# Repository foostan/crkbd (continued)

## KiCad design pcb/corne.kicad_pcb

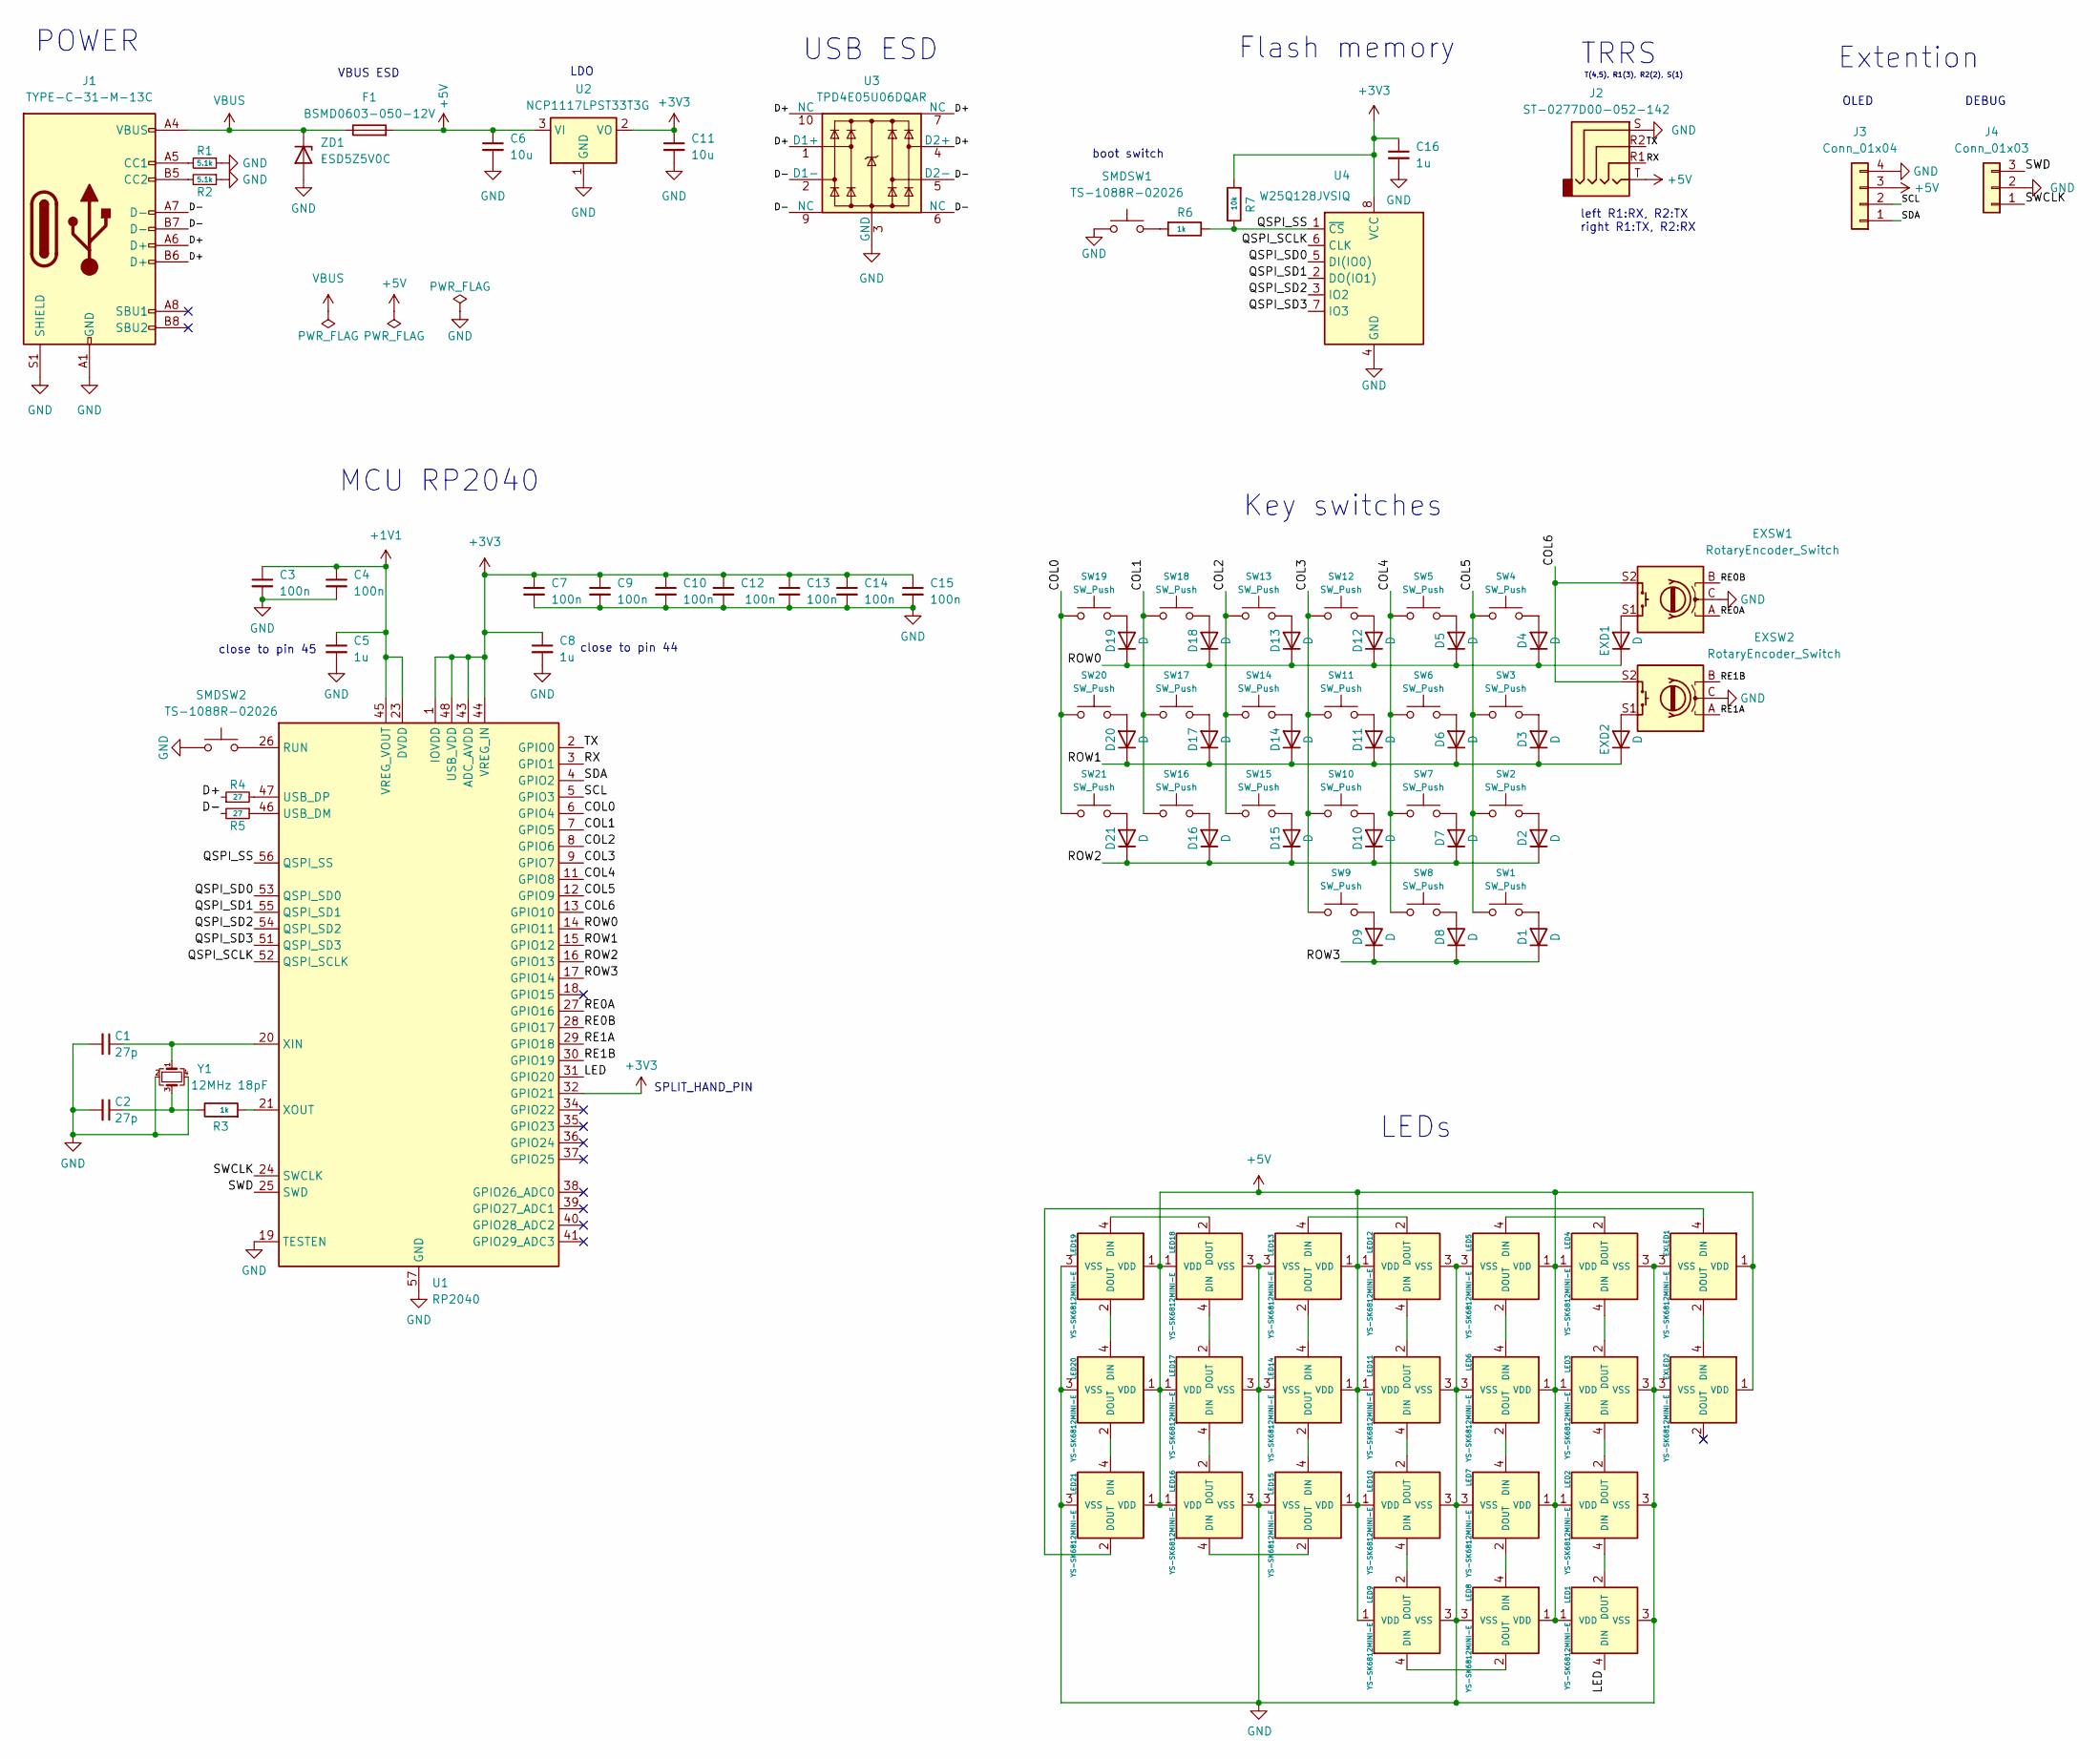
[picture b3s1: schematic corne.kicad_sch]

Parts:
C1, C2: 27p; C_0402_1005Metric
C3, C4, C7, C9, C10, C12, C13, C14, C15: 100n; C_0402_1005Metric
C5, C8, C16: 1u; C_0402_1005Metric
C6, C11: 10u; C_0402_1005Metric
D1, D2, D3, D4, D5, D6, D7, D8, D9, D10, D11, D12, D13, D14, D15, D16, D17, D18, D19, D20, D21: D; D_0603_1608Metric
EXD1, EXD2: D; D_0603_1608Metric
EXLED1, EXLED2: YS-SK6812MINI-E
EXSW1, EXSW2: RotaryEncoder_Switch; keyswitch_cherrymx_hotswap_1u_rotary_encoder_ec12
F1: BSMD0603-050-12V; Fuse_0603_1608Metric; JLCPCB Part # C2844464
J1: TYPE-C-31-M-13C; JLCPCB Part # C2848620
J2: ST-0277D00-052-142; JLCPCB Part # C2837093
J3: Conn_01x04; OLED
J4: Conn_01x03; PinHeader_1x03_P2.54mm_Vertical
LED1, LED2, LED3, LED4, LED5, LED6, LED7, LED8, LED9, LED10, LED11, LED12, LED13, LED14, LED15, LED16, LED17, LED18, LED19, LED20, LED21: YS-SK6812MINI-E
R1, R2: 5.1k; R_0603_1608Metric
R3, R6: 1k; R_0603_1608Metric
R4, R5: 27; R_0603_1608Metric
R7: 10k; R_0603_1608Metric
SMDSW1, SMDSW2: TS-1088R-02026; JLCPCB Part # C455280
SW1: SW_Push; keyswitch_cherrymx_hotswap_1.5u
SW2, SW3, SW4, SW5, SW6, SW7, SW8, SW9, SW10, SW11, SW12, SW13, SW14, SW15, SW16, SW17, SW18, SW19, SW20, SW21: SW_Push; keyswitch_cherrymx_hotswap_1u
U1: RP2040; QFN-56-1EP_7x7mm_P0.4mm_EP3.2x3.2mm; JLCPCB Part # C2040
U2: NCP1117LPST33T3G; SOT-223-3_TabPin2; JLCPCB Part # C146799
U3: TPD4E05U06DQAR; USON-10_2.5x1.0mm_P0.5mm; JLCPCB Part # C138714
U4: W25Q128JVSIQ; SOIC-8_5.23x5.23mm_P1.27mm; JLCPCB Part # C113767
Y1: 12MHz 18pF; Crystal_SMD_3225-4Pin_3.2x2.5mm; MFR.Part # Q22FA23V0041800; JLCPCB Part # C91749
ZD1: ESD5Z5V0C; D_SOD-523; JLCPCB Part # C2901325

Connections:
+1V1: C3.1, C4.1, C5.1, U1.23 (DVDD), U1.45 (VREG_VOUT), U1.50 (DVDD)
+3V3: C7.1, C8.1, C9.1, C10.1, C11.1, C12.1, C13.1, C14.1, C15.1, C16.1, R7.2, U1.1 (IOVDD), U1.10 (IOVDD), U1.22 (IOVDD), U1.32 (GPIO21), U1.33 (IOVDD), U1.42 (IOVDD), U1.43 (ADC_AVDD), U1.44 (VREG_IN), U1.48 (USB_VDD), U1.49 (IOVDD), U2.2 (VO), U4.8 (VCC)
+5V: C6.1, EXLED1.1 (VDD), EXLED2.1 (VDD), F1.2, J2.T, J3.3, LED1.1 (VDD), LED2.1 (VDD), LED3.1 (VDD), LED4.1 (VDD), LED5.1 (VDD), LED6.1 (VDD), LED7.1 (VDD), LED8.1 (VDD), LED9.1 (VDD), LED10.1 (VDD), LED11.1 (VDD), LED12.1 (VDD), LED13.1 (VDD), LED14.1 (VDD), LED15.1 (VDD), LED16.1 (VDD), LED17.1 (VDD), LED18.1 (VDD), LED19.1 (VDD), LED20.1 (VDD), LED21.1 (VDD), U2.3 (VI)
/COL0: SW19.1, SW20.1, SW21.1, U1.6 (GPIO4)
/COL1: SW16.1, SW17.1, SW18.1, U1.7 (GPIO5)
/COL2: SW13.1, SW14.1, SW15.1, U1.8 (GPIO6)
/COL3: SW9.1, SW10.1, SW11.1, SW12.1, U1.9 (GPIO7)
/COL4: SW5.1, SW6.1, SW7.1, SW8.1, U1.11 (GPIO8)
/COL5: SW1.1, SW2.1, SW3.1, SW4.1, U1.12 (GPIO9)
/COL6: EXSW1.S2, EXSW2.S2, U1.13 (GPIO10)
/D+: J1.A6 (D+), J1.B6 (D+), R4.1, U3.1 (D1+), U3.4 (D2+), U3.7 (NC), U3.10 (NC)
/D-: J1.A7 (D-), J1.B7 (D-), R5.2, U3.2 (D1-), U3.5 (D2-), U3.6 (NC), U3.9 (NC)
/LED: LED1.4 (DIN), U1.31 (GPIO20)
/QSPI_SCLK: U1.52 (QSPI_SCLK), U4.6 (CLK)
/QSPI_SD0: U1.53 (QSPI_SD0), U4.5 (DI(IO0))
/QSPI_SD1: U1.55 (QSPI_SD1), U4.2 (DO(IO1))
/QSPI_SD2: U1.54 (QSPI_SD2), U4.3 (IO2)
/QSPI_SD3: U1.51 (QSPI_SD3), U4.7 (IO3)
/QSPI_SS: R6.1, R7.1, U1.56 (QSPI_SS), U4.1 (~CS)
/RE0A: EXSW1.A, U1.27 (GPIO16)
/RE0B: EXSW1.B, U1.28 (GPIO17)
/RE1A: EXSW2.A, U1.29 (GPIO18)
/RE1B: EXSW2.B, U1.30 (GPIO19)
/ROW0: D4.1 (K), D5.1 (K), D12.1 (K), D13.1 (K), D18.1 (K), D19.1 (K), EXD1.1 (K), U1.14 (GPIO11)
/ROW1: D3.1 (K), D6.1 (K), D11.1 (K), D14.1 (K), D17.1 (K), D20.1 (K), EXD2.1 (K), U1.15 (GPIO12)
/ROW2: D2.1 (K), D7.1 (K), D10.1 (K), D15.1 (K), D16.1 (K), D21.1 (K), U1.16 (GPIO13)
/ROW3: D1.1 (K), D8.1 (K), D9.1 (K), U1.17 (GPIO14)
/RX: J2.R1, U1.3 (GPIO1)
/SCL: J3.2, U1.5 (GPIO3)
/SDA: J3.1, U1.4 (GPIO2)
/SWCLK: J4.1, U1.24 (SWCLK)
/SWD: J4.3, U1.25 (SWD)
/TX: J2.R2, U1.2 (GPIO0)
GND: C1.2, C2.2, C3.2, C4.2, C5.2, C6.2, C7.2, C8.2, C9.2, C10.2, C11.2, C12.2, C13.2, C14.2, C15.2, C16.2, EXLED1.3 (VSS), EXLED2.3 (VSS), EXSW1.C, EXSW2.C, J1.A1 (GND), J1.A12 (GND), J1.B1 (GND), J1.B12 (GND), J1.S1 (SHIELD), J2.S, J3.4, J4.2, LED1.3 (VSS), LED2.3 (VSS), LED3.3 (VSS), LED4.3 (VSS), LED5.3 (VSS), LED6.3 (VSS), LED7.3 (VSS), LED8.3 (VSS), LED9.3 (VSS), LED10.3 (VSS), LED11.3 (VSS), LED12.3 (VSS), LED13.3 (VSS), LED14.3 (VSS), LED15.3 (VSS), LED16.3 (VSS), LED17.3 (VSS), LED18.3 (VSS), LED19.3 (VSS), LED20.3 (VSS), LED21.3 (VSS), R1.1, R2.1, SMDSW1.1, SMDSW2.1, U1.19 (TESTEN), U1.57 (GND), U2.1 (GND), U3.3 (GND), U3.8 (GND), U4.4 (GND), Y1.2, Y1.4, ZD1.2 (A)
unnamed: C2.1, R3.1, Y1.3
unnamed: D1.2 (A), SW1.2
unnamed: D2.2 (A), SW2.2
unnamed: D3.2 (A), SW3.2
unnamed: D4.2 (A), SW4.2
unnamed: D5.2 (A), SW5.2
unnamed: D6.2 (A), SW6.2
unnamed: D7.2 (A), SW7.2
unnamed: D8.2 (A), SW8.2
unnamed: D9.2 (A), SW9.2
unnamed: D10.2 (A), SW10.2
unnamed: D11.2 (A), SW11.2
unnamed: D12.2 (A), SW12.2
unnamed: D13.2 (A), SW13.2
unnamed: D14.2 (A), SW14.2
unnamed: D15.2 (A), SW15.2
unnamed: D16.2 (A), SW16.2
unnamed: D17.2 (A), SW17.2
unnamed: D18.2 (A), SW18.2
unnamed: D19.2 (A), SW19.2
unnamed: D20.2 (A), SW20.2
unnamed: D21.2 (A), SW21.2
unnamed: EXD1.2 (A), EXSW1.S1
unnamed: EXD2.2 (A), EXSW2.S1
unnamed: EXLED1.4 (DIN), LED21.2 (DOUT)
unnamed: EXLED1.2 (DOUT), EXLED2.4 (DIN)
unnamed: J1.A5 (CC1), R1.2
unnamed: J1.B5 (CC2), R2.2
unnamed: LED1.2 (DOUT), LED2.4 (DIN)
unnamed: LED2.2 (DOUT), LED3.4 (DIN)
unnamed: LED3.2 (DOUT), LED4.4 (DIN)
unnamed: LED4.2 (DOUT), LED5.4 (DIN)
unnamed: LED5.2 (DOUT), LED6.4 (DIN)
unnamed: LED6.2 (DOUT), LED7.4 (DIN)
unnamed: LED7.2 (DOUT), LED8.4 (DIN)
unnamed: LED8.2 (DOUT), LED9.4 (DIN)
unnamed: LED9.2 (DOUT), LED10.4 (DIN)
unnamed: LED10.2 (DOUT), LED11.4 (DIN)
unnamed: LED11.2 (DOUT), LED12.4 (DIN)
unnamed: LED12.2 (DOUT), LED13.4 (DIN)
unnamed: LED13.2 (DOUT), LED14.4 (DIN)
unnamed: LED14.2 (DOUT), LED15.4 (DIN)
unnamed: LED15.2 (DOUT), LED16.4 (DIN)
unnamed: LED16.2 (DOUT), LED17.4 (DIN)
unnamed: LED17.2 (DOUT), LED18.4 (DIN)
unnamed: LED18.2 (DOUT), LED19.4 (DIN)
unnamed: LED19.2 (DOUT), LED20.4 (DIN)
unnamed: LED20.2 (DOUT), LED21.4 (DIN)
unnamed: R6.2, SMDSW1.2
unnamed: SMDSW2.2, U1.26 (RUN)
unnamed: R5.1, U1.46 (USB_DM)
unnamed: R4.2, U1.47 (USB_DP)
unnamed: C1.1, U1.20 (XIN), Y1.1
unnamed: R3.2, U1.21 (XOUT)
VBUS: F1.1, J1.A4 (VBUS), J1.A9 (VBUS), J1.B4 (VBUS), J1.B9 (VBUS), ZD1.1 (K)

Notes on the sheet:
TRRS
left R1:RX, R2:TX right R1:TX, R2:RX
POWER
close to pin 44
T(4,5), R1(3), R2(2), S(1)
LDO
USB ESD
boot switch
DEBUG
Key switches
SPLIT_HAND_PIN
Flash memory
close to pin 45
Extention
LEDs
MCU RP2040
VBUS ESD
OLED

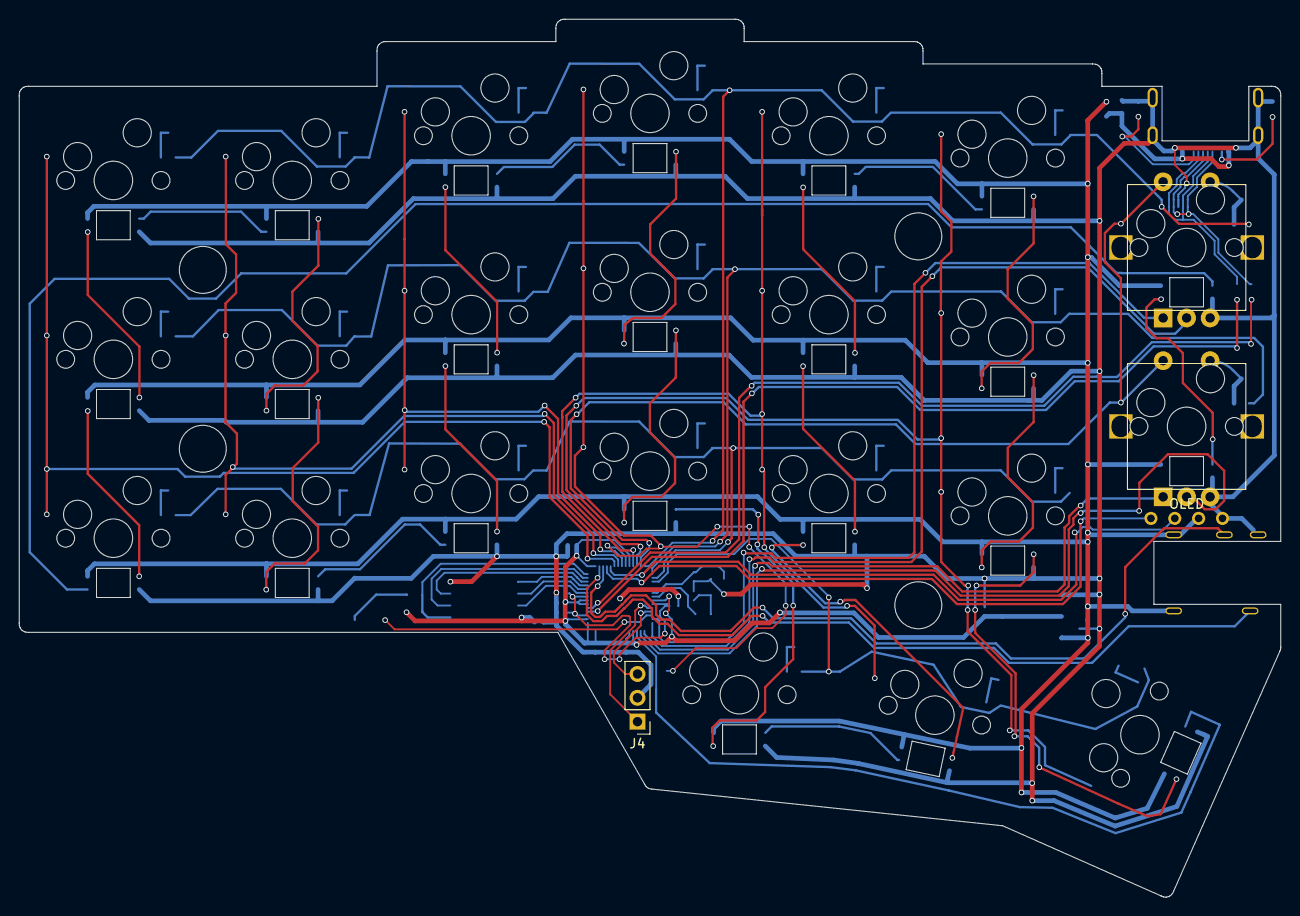
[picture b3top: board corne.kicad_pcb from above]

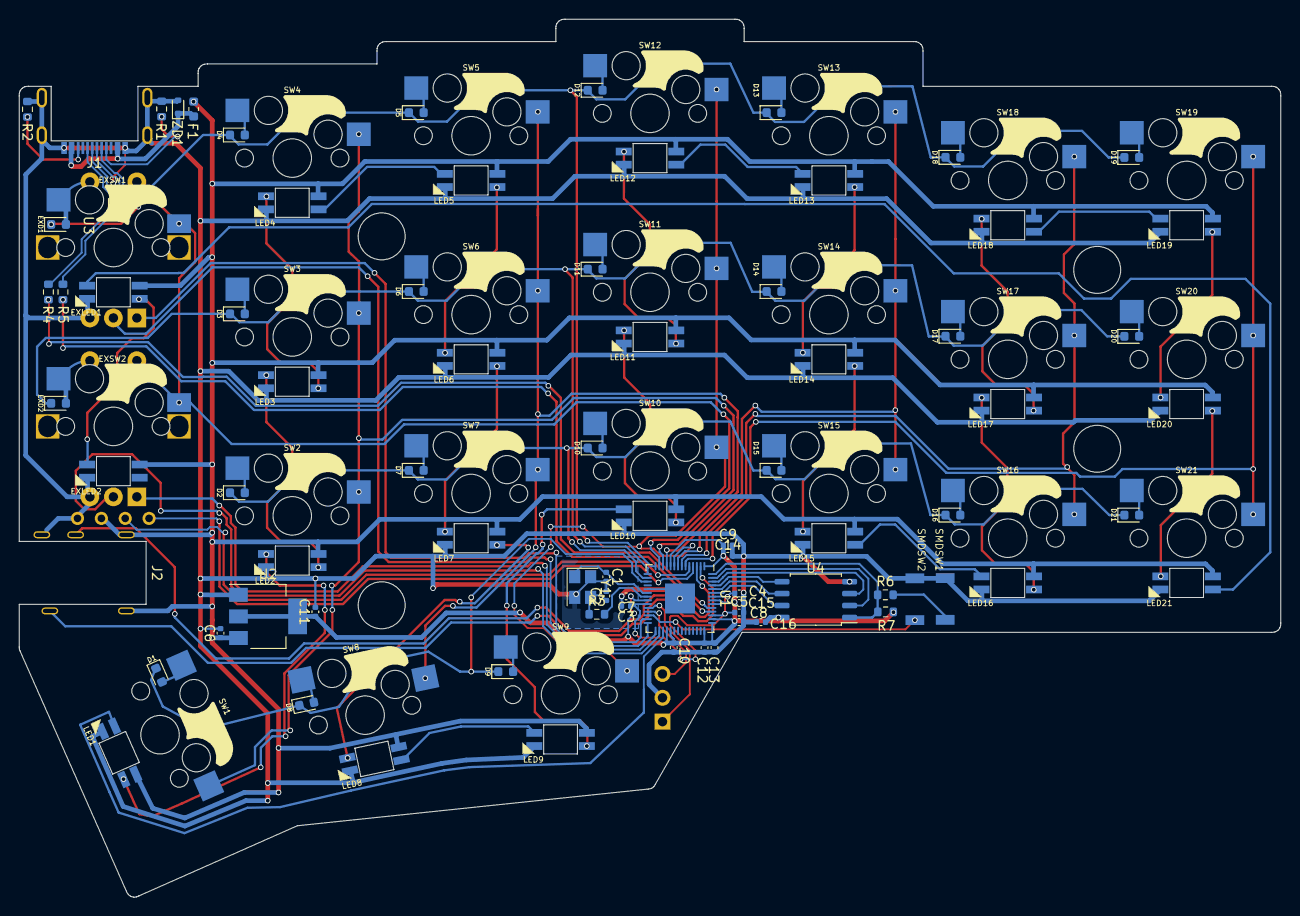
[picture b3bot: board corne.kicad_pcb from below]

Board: 2 copper layers, 134.3 x 93.5 mm, 105 parts (80 on the bottom side), 89 nets.

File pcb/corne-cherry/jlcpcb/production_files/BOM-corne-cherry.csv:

Comment,Designator,Footprint,LCSC
W25Q128JVSIQ,"U4,rU4",SOIC-8_5.23x5.23mm_P1.27mm,C113767
1k,"R3,R6,rR3,rR6",R_0402_1005Metric,C11702
TPD4E05U06DQAR,"U3,rU3",USON-10_2.5x1.0mm_P0.5mm,C138714
NCP1117LPST33T3G,"U2,rU2",SOT-223-3_TabPin2,C146799
100n,"C10,C12,C13,C14,C15,C3,C4,C7,C9,rC10,rC12,rC13,rC14,rC15,rC3,rC4,rC7,rC9",C_0402_1005Metric,C1525
10u,"C11,C6,rC11,rC6",C_0402_1005Metric,C15525
27p,"C1,C2,rC1,rC2",C_0402_1005Metric,C1557
RP2040,"U1,rU1",QFN-56-1EP_7x7mm_P0.4mm_EP3.2x3.2mm,C2040
1N4148WT,"D1,rD1",D_SOD-523,C232841
10k,"R7,rR7",R_0402_1005Metric,C25744
5.1k,"R1,R2,rR1,rR2",R_0402_1005Metric,C25905
ST-0277D00-052-142,"J2,rJ2",ST-0277D00-052-142,C2837093
BSMD0603-050-12V,"F1,rF1",Fuse_0603_1608Metric,C2844464
TYPE-C-31-M-13C,"J1,rJ1",TYPE-C-31-M-13C,C2848620
ESD5Z5V0C,"ZD1,rZD1",D_SOD-523,C2901325
27,"R4,R5,rR4,rR5",R_0402_1005Metric,C2909343
TS-1088R-02026,"SMDSW1,SMDSW2,rSMDSW1,rSMDSW2",TS-1088R-02026,C455280
RotaryEncoder_Switch,"EXSW1,EXSW2,SW1,SW10,SW11,SW12,SW13,SW14,SW15,SW16,SW17,SW18,SW19,SW2,SW20,SW21,SW3,SW4,SW5,SW6,SW7,SW8,SW9,rEXSW1,rEXSW2,rSW1,rSW10,rSW11,rSW12,rSW13,rSW14,rSW15,rSW16,rSW17,rSW18,rSW19,rSW2,rSW20,rSW21,rSW3,rSW4,rSW5,rSW6,rSW7,rSW8,rSW9",keyswitch_cherrymx_hotswap_1u_rotary_encoder_ec12,C5156480
1u,"C16,C5,C8,rC16,rC5,rC8",C_0402_1005Metric,C52923
12MHz 18pF,"Y1,rY1",Crystal_SMD_3225-4Pin_3.2x2.5mm,C91749
YS-SK6812MINI-E,LED16,YS-SK6812MINI-E,C5149201
YS-SK6812MINI-E,rLED16,YS-SK6812MINI-E,C5149201
YS-SK6812MINI-E,LED3,YS-SK6812MINI-E,C5149201
YS-SK6812MINI-E,rLED4,YS-SK6812MINI-E,C5149201
YS-SK6812MINI-E,LED17,YS-SK6812MINI-E,C5149201
YS-SK6812MINI-E,rLED6,YS-SK6812MINI-E,C5149201
YS-SK6812MINI-E,LED5,YS-SK6812MINI-E,C5149201
YS-SK6812MINI-E,rLED2,YS-SK6812MINI-E,C5149201
YS-SK6812MINI-E,LED8,YS-SK6812MINI-E,C5149201
YS-SK6812MINI-E,LED10,YS-SK6812MINI-E,C5149201
YS-SK6812MINI-E,rLED20,YS-SK6812MINI-E,C5149201
YS-SK6812MINI-E,LED12,YS-SK6812MINI-E,C5149201
YS-SK6812MINI-E,rLED15,YS-SK6812MINI-E,C5149201
YS-SK6812MINI-E,LED20,YS-SK6812MINI-E,C5149201
YS-SK6812MINI-E,rEXLED1,YS-SK6812MINI-E,C5149201
YS-SK6812MINI-E,rLED17,YS-SK6812MINI-E,C5149201
YS-SK6812MINI-E,rLED19,YS-SK6812MINI-E,C5149201
YS-SK6812MINI-E,LED15,YS-SK6812MINI-E,C5149201
YS-SK6812MINI-E,LED1,YS-SK6812MINI-E,C5149201
YS-SK6812MINI-E,rLED5,YS-SK6812MINI-E,C5149201
YS-SK6812MINI-E,rLED8,YS-SK6812MINI-E,C5149201
YS-SK6812MINI-E,rLED13,YS-SK6812MINI-E,C5149201
YS-SK6812MINI-E,LED13,YS-SK6812MINI-E,C5149201
YS-SK6812MINI-E,LED21,YS-SK6812MINI-E,C5149201
YS-SK6812MINI-E,LED19,YS-SK6812MINI-E,C5149201
YS-SK6812MINI-E,LED7,YS-SK6812MINI-E,C5149201
YS-SK6812MINI-E,rLED14,YS-SK6812MINI-E,C5149201
YS-SK6812MINI-E,rLED9,YS-SK6812MINI-E,C5149201
YS-SK6812MINI-E,EXLED2,YS-SK6812MINI-E,C5149201
YS-SK6812MINI-E,LED9,YS-SK6812MINI-E,C5149201
YS-SK6812MINI-E,EXLED1,YS-SK6812MINI-E,C5149201
YS-SK6812MINI-E,LED6,YS-SK6812MINI-E,C5149201
YS-SK6812MINI-E,rLED10,YS-SK6812MINI-E,C5149201
YS-SK6812MINI-E,rLED12,YS-SK6812MINI-E,C5149201
YS-SK6812MINI-E,rLED11,YS-SK6812MINI-E,C5149201
YS-SK6812MINI-E,rLED21,YS-SK6812MINI-E,C5149201
YS-SK6812MINI-E,rLED3,YS-SK6812MINI-E,C5149201
YS-SK6812MINI-E,LED11,YS-SK6812MINI-E,C5149201
YS-SK6812MINI-E,rEXLED2,YS-SK6812MINI-E,C5149201
YS-SK6812MINI-E,LED2,YS-SK6812MINI-E,C5149201
YS-SK6812MINI-E,LED14,YS-SK6812MINI-E,C5149201
YS-SK6812MINI-E,rLED1,YS-SK6812MINI-E,C5149201
YS-SK6812MINI-E,LED18,YS-SK6812MINI-E,C5149201
YS-SK6812MINI-E,LED4,YS-SK6812MINI-E,C5149201
YS-SK6812MINI-E,rLED7,YS-SK6812MINI-E,C5149201
YS-SK6812MINI-E,rLED18,YS-SK6812MINI-E,C5149201

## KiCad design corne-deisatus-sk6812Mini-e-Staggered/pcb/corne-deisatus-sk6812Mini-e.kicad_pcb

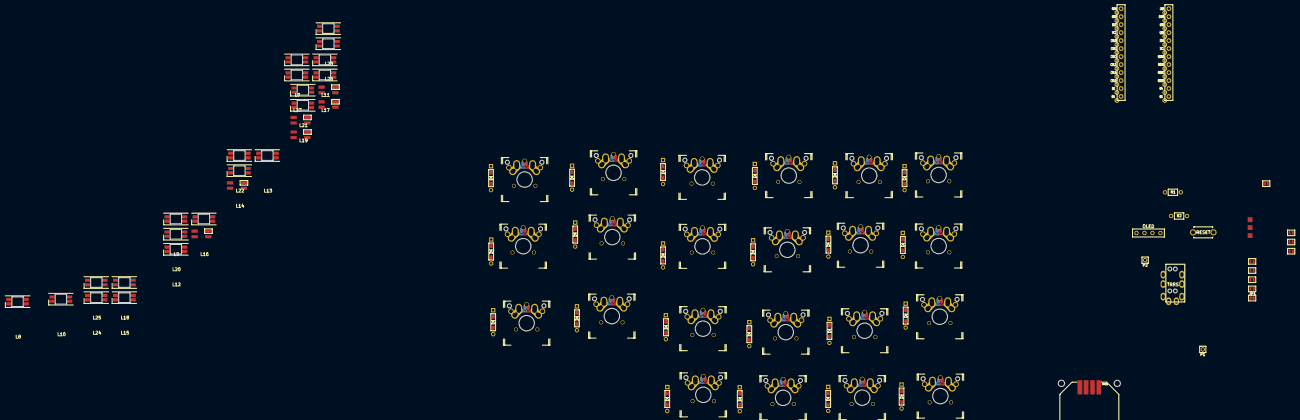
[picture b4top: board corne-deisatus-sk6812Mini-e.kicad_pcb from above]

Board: 2 copper layers, 90 parts (0 on the bottom side), 73 nets, no tracks yet.

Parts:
D1, D2, D3, D4, D5, D6, D7, D8, D9, D10, D11, D12, D13, D14, D15, D16, D17, D18, D19, D20, D21, D22: D; D3_TH_SMD
J1: MJ-4PP-9
J2: OLED
J3: LED; StripLED_rev
JP1: JP
JP2, JP3, JP4, JP5, JP6, JP7, JP8, JP9: Jumper
L1, L2, L3, L4, L5, L6: SK6812MINI; SK6812MINI_underglow_rev
L7, L8, L9, L10, L11, L12, L13, L14, L15, L16, L17, L18, L19, L20, L21, L22, L23, L24, L25, L26, L27: SK6812MINI-E; YS-SK6812MINI-E
P1, P2: i2c-pin; 1pin_conn
R1, R2: R
RSW1: SW_PUSH; ResetSW
RV11: JOYSTICK-PSP1000; JOYSTICK-PSP1000-reverse
SW1, SW2, SW3, SW4, SW5, SW6, SW7, SW8, SW9, SW10, SW11, SW12, SW13, SW14, SW15, SW16, SW17, SW18, SW19, SW21, SW22: SW_PUSH; MX-ALPS-Choc-X-straight-crane2
SW20: SW_PUSH; MX-ALPS-Choc-X-straight-crane2-u1.25
U1: ProMicro; ProMicro_v2

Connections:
AnalogX: RV11.1, U1.12
AnalogY: RV11.3, U1.11
GND: J1.C, J3.1, JP2.1, JP9.1, L1.2, L2.2, L3.2, L4.2, L5.2, L6.2, L7.3, L8.3, L9.3, L10.3, L11.3, L12.3, L13.3, L14.3, L15.3, L16.3, L17.3, L18.3, L19.3, L20.3, L21.3, L22.3, L23.3, L24.3, L25.3, L26.3, L27.3, RSW1.2, RV11.2, U1.3, U1.4, U1.23
LED: J3.2, L3.3, U1.1
unnamed: D1.2, SW1.2
unnamed: D2.2, SW2.2
unnamed: D3.2, SW3.2
unnamed: D4.2, SW4.2
unnamed: D5.2, SW5.2
unnamed: D6.2, SW6.2
unnamed: D7.2, SW7.2
unnamed: D8.2, SW8.2
unnamed: D9.2, SW9.2
unnamed: D10.2, SW10.2
unnamed: D11.2, SW11.2
unnamed: D12.2, SW12.2
unnamed: D13.2, SW13.2
unnamed: D14.2, SW14.2
unnamed: D15.2, SW15.2
unnamed: D16.2, SW16.2
unnamed: D17.2, SW17.2
unnamed: D18.2, SW18.2
unnamed: D19.2, SW20.2
unnamed: D20.2, SW21.2
unnamed: D21.2, SW22.2
unnamed: D22.2, SW19.2
unnamed: J1.A, P1.1
unnamed: J1.B, JP1.2, P2.1
unnamed: J2.1, JP5.2, JP9.2
unnamed: J2.2, JP4.2, JP8.2
unnamed: J2.3, JP3.2, JP7.2
unnamed: J2.4, JP2.2, JP6.2
unnamed: L1.1, L4.3
unnamed: L1.3, L2.1
unnamed: L2.3, L3.1
unnamed: L4.1, L5.3
unnamed: L5.1, L6.3
unnamed: L7.4, L8.2
unnamed: L9.4, L10.2
unnamed: L10.4, L16.2
unnamed: L11.2, L17.4
unnamed: L11.4, L12.2
unnamed: L12.4, L18.2
unnamed: L13.2, L19.4
unnamed: L7.2, L13.4
unnamed: L8.4, L14.2
unnamed: L14.4, L20.2
unnamed: L15.2, L21.4
unnamed: L9.2, L15.4
unnamed: L16.4, L22.2
unnamed: L17.2, L23.4
unnamed: L18.4, L24.2
unnamed: L20.4, L21.2
unnamed: L22.4, L25.2
unnamed: L23.2, L26.4
unnamed: L24.4, L27.2
unnamed: L25.4, L26.2
unnamed: L6.1, L27.4
SCL: JP4.1, JP7.1, R2.2, U1.6
SDA: JP5.1, JP6.1, R1.2, U1.5
VCC: J1.D, J3.3, JP3.1, JP8.1, L1.4, L2.4, L3.4, L4.4, L5.4, L6.4, L7.1, L8.1, L9.1, L10.1, L11.1, L12.1, L13.1, L14.1, L15.1, L16.1, L17.1, L18.1, L19.1, L20.1, L21.1, L22.1, L23.1, L24.1, L25.1, L26.1, L27.1, R1.1, R2.1, RV11.4, U1.21
col0: SW1.1, SW7.1, SW13.1, U1.20
col1: SW2.1, SW8.1, SW14.1, U1.19
col2: SW3.1, SW9.1, SW15.1, SW19.1, U1.18
col3: SW4.1, SW10.1, SW16.1, SW20.1, U1.17
col4: SW5.1, SW11.1, SW17.1, SW21.1, U1.16
col5: SW6.1, SW12.1, SW18.1, SW22.1, U1.15
data: JP1.1, U1.2
reset: RSW1.1, U1.22
row0: D1.1, D2.1, D3.1, D4.1, D5.1, D6.1, U1.7
row1: D7.1, D8.1, D9.1, D10.1, D11.1, D12.1, U1.8
row2: D13.1, D14.1, D15.1, D16.1, D17.1, D18.1, U1.9
row3: D19.1, D20.1, D21.1, D22.1, U1.10

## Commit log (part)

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2019-02-22 Update buildguide_tilting_tenting_plate_jp.md
    非対応分を明確に修正
2019-03-30 Update pretties
2019-03-30 Remove backup file
2019-07-14 outline-fix
2019-07-29 Add new footprints
2019-10-02 Update LICENSE
2019-10-02 Move acrylic_plate
2019-10-02 Add plate for mini
2019-10-10 Added info on SMD diode polarity to english build guide.
2019-10-10 Added clearer ProMicro orientation instructions to the english build guide.
2019-10-10 Added more info on testing to the english builde guide.
2019-10-10 Added a troubleshoot section to the english build guide.
2019-11-04 corne-light-rev1.1.0
2019-11-26 Add build-guide for corne-light
2019-11-26 Add top-plate for light
2019-12-06 Update light
2019-12-13 fixed typo
2020-02-11 Add cherry+ top-middle plate
2020-02-11 Move case/acrylic_plate to plates
2020-04-13 Add kailh low profiile
2020-05-19 Add tenting mini crkbrd version
2020-06-26 gitignore: simplify _gerber_ dir exclusion
    gitignore globs are not repo-global by default.
    They are so only with an explicit `/` in front.
    Also, all files below an ignored directory
    are ignored as well.
2020-06-26 git ignore more files created by KiCAD (& co.)
2020-07-07 Improve Corne Chocolate EN build-guide (was google-translated)
    Apart form language, it also fixes formatting, so some links,
    images and code-blocks are now shown as they should.
2020-07-07 README: Adds links to the build guides
2020-08-01 [GitHub] Add release gerber files workflow
2020-08-04 Update cuts and footprints
2020-09-04 Move libralies to kicad-symbols dir
2020-09-04 Add kicad-packages3D
2020-09-04 Add git file
2020-09-04 Move kbd.pretty to kicad-footprints
2020-09-04 Fix cd dir
2020-09-04 Update the description of MJ-4PP-9
2020-09-04 Add sym-lib-table and checking it flow
2020-09-04 Update order of flow
2020-09-05 Fix syntax and order
2020-09-05 Ignore kicad-library-utils
2020-09-05 Update LICENSE to be included foostan only
2020-09-05 Add README.md
2020-09-05 Update pcb plates
2020-09-05 Update acrylic plates
2020-09-05 Cleanup
2020-09-05 Add git-submodule
2020-09-05 Update lib tables
2020-09-27 Update the build guide for corne cherry v3
2020-09-27 Update guides
2020-09-27 Add kicad-packages3D models
2020-09-27 Add logo
2020-09-27 Remove logo
2020-09-29 Remove YS prefix
2020-10-02 Fix tilting doc path
2020-10-13 Update libs of corne-light
2020-10-13 Move to current docs to v1
2020-10-13 Add the doc for corne-light-low-edition
2020-11-03 Add alps compatible switche footprint
2020-11-03 Add 3d files
2020-11-03 Update firmware documentations
2020-11-03 Fix link
2020-11-03 Update links
2020-11-03 Add PCB-SVG of Corne Cherry v3.0.0
2020-11-03 Add new footprint for thread
2020-11-03 Add 3d model
2020-11-03 Update submodules
2020-11-03 Update kbd footprints
2020-11-13 Create or Update plate data for corne-light
2020-11-13 Update pcb
2020-11-13 Update corne light plates
2020-11-14 Add add holes for mini
2020-12-08 Update the link of firmware to latest
2021-01-14 removed break off cuts
2021-01-20 reverted corne classic to original, made new folder
2021-01-20 added new footprints and outline
2021-01-21 Turn Choc key socket footprint 180 degree.
2021-01-21 working on tracks
2021-01-22 mostly done
2021-01-22 added all tracks except GND
2021-01-22 every thing connected
2021-01-23 Update buildguide_en.md typo fix
    Minor cleanup commit fixing a typo wholes -> holes) in the English build guide.
2021-02-03 fixed pinout, changed LED type
2021-02-03 made led reversable
2021-02-03 added new pcb for new leds
2021-02-03 Updated PCB for new pins
2021-02-03 tracks done
2021-02-03 removed unneeded cuts, updated gerber
2021-02-15 added footprint
2021-04-17 Improves MarkDown standards conformity
2021-04-17 Converts pseudo-headers into real ones
2021-04-17 README: Minor white-space cleanup
2021-04-29 Correct minor typo in buildguide_en.md
2021-05-15 Unifies table headers
2021-05-15 Add all missing English translations of MD documents
    ... using Google translate + manual MD syntax fixing
2021-05-15 Fixes paths to 3 images
2021-05-15 Unifies instructions a bit, and improves grammar and wording
2021-06-29 edited .plates/common/*.svg to make them working with inkscape
2021-06-29 added more .svg files
2021-08-24 Fix the outlines of classic
2021-09-24 joined nodes of plate's outline path
2021-11-07 Update README.md
    https://forum.kicad.info/t/warning-avoid-all-links-to-kicad-pcb-org-use-kicad-org/31521
2021-12-26 Update gitignore for kicad6
2022-02-16 Adds SPDX license info (REUSE compliance)
2022-02-16 README: Adds the REUSE badge
2022-03-09 Update KiCad EDA links
2022-03-16 initial
2022-03-29 update firmware reference + more build guide things
2022-04-07 Fix the PCB outline of chocolate
2022-06-04 rename dirs
2022-07-18 first workflow
2022-12-11 Finished wiring
2022-12-11 Fixed unconnected components
2022-12-11 Fixed proper sizing and rerouted
2022-12-12 Added keebio symbols and footprints
2023-01-04 cherry
2023-01-04 chocolate
2023-01-04 light
2023-01-04 plates
2023-06-24 Fix wrong path in Makefile
2023-06-24 Use project relative paths to 3d models
2023-06-24 Clean up old footprints
2023-07-14 Update hotswap switches
2023-07-14 Squashed 'corne-chocolate/pcb/kbd/' content from commit 9646f49
    git-subtree-dir: corne-chocolate/pcb/kbd
    git-subtree-split: 9646f492fff643907c0444ce62bd6eb57c50b4bc
2023-07-14 Squashed 'corne-classic/pcb/kbd/' content from commit 9646f49
    git-subtree-dir: corne-classic/pcb/kbd
    git-subtree-split: 9646f492fff643907c0444ce62bd6eb57c50b4bc
2023-07-14 Update Makefile
2023-07-14 Squashed 'pcb/kbd/' content from commit 00201b6
    git-subtree-dir: pcb/kbd
    git-subtree-split: 00201b6ef2bc9ab2800b878e3095ed44aeda937a
2023-09-23 Add rotary encoder
2023-09-23 Squashed 'pcb/kbd/' changes from 00201b6..da6b024
    da6b024 Delete unused footprint
    00d6f0c Add rotary encoder
    git-subtree-dir: pcb/kbd
    git-subtree-split: da6b024aa2958eb2353cbe3a6dc57dd9080cd656
2023-09-23 Add the 3D model of TYPE-C-31-M-13C
2023-09-23 Add assigns
2023-09-23 Squashed 'pcb/kbd/' changes from da6b024..9711222
    9711222 Add the 3D model of TYPE-C-31-M-13C
    ee44fbc Add footprint of TYPE-C-31-M-13C
    git-subtree-dir: pcb/kbd
    git-subtree-split: 9711222e7868c834901f35864b34dba3f8a3dc2b
2023-09-23 Squashed 'pcb/kbd/' changes from 9711222..8cc619e
    8cc619e Add ST-0277D00-052-142
    git-subtree-dir: pcb/kbd
    git-subtree-split: 8cc619ee7e99e89baa22aea76c0537ca33a052b2
2023-09-23 Fix pin number
2023-09-24 Update CrtYd
2023-09-24 Squashed 'pcb/kbd/' changes from b354fc0..ab94e05
    ab94e05 Update CrtYd
    git-subtree-dir: pcb/kbd
    git-subtree-split: ab94e0527a5daed7194a657752393e780a8e40ef
2023-09-26 Squashed 'pcb/kbd/' changes from ab94e05..57d0a68
    57d0a68 Add smd switch
    git-subtree-dir: pcb/kbd
    git-subtree-split: 57d0a6803ee76549f20bb3601fda7103a485a96c
2023-09-27 Add mergin area
2023-09-27 Squashed 'pcb/kbd/' changes from 57d0a68..3a51036
    3a51036 Add mergin area
    git-subtree-dir: pcb/kbd
    git-subtree-split: 3a51036ff6c0d2511e5c2c71c14746ac71c4f29a
2023-09-30 Fix positions
2023-09-30 Squashed 'pcb/kbd/' changes from 3a51036..1e68599
    1e68599 Fix positions
    git-subtree-dir: pcb/kbd
    git-subtree-split: 1e6859946104ea7de8c202f10c3c8eddc143db14
2023-09-30 Fix pad positions
2023-09-30 Squashed 'pcb/kbd/' changes from 1e68599..a1a5b18
    a1a5b18 Fix pad positions
    git-subtree-dir: pcb/kbd
    git-subtree-split: a1a5b18d8f7a5969aae8d740563d380ecc7f5430
2023-09-30 Squashed 'pcb/kbd/' changes from a1a5b18..a2fdf46
    a2fdf46 Update lines
    git-subtree-dir: pcb/kbd
    git-subtree-split: a2fdf4689355d9eec99c518ad68d304fb75dfe0b
2023-09-30 Update positions
2023-09-30 Squashed 'pcb/kbd/' changes from a2fdf46..148d932
    148d932 Fix footprint type
    git-subtree-dir: pcb/kbd
    git-subtree-split: 148d9328eeec21db74b07cd60d3d3c1f7de27ad5
2023-09-30 Fix some errors
2023-09-30 Squashed 'pcb/kbd/' changes from 148d932..043d4bd
    043d4bd Update pad positions
    git-subtree-dir: pcb/kbd
    git-subtree-split: 043d4bd18d2ea93479190ac4e489e7355e124a9e
2023-10-01 Finish left hand
2023-10-04 Fix attr
2023-10-04 Squashed 'pcb/kbd/' changes from affd835..fe5de30
    fe5de30 Add parts area
    0f5ea3b Fix attr
    git-subtree-dir: pcb/kbd
    git-subtree-split: fe5de303769462056fd0c544a8fa1ca451ca1390
2023-10-05 Fix the `nerdyscout/kicad-exports` schema args
2023-10-05 Upgade `nerdyscout/kicad-exports` to v2.2
2023-10-05 Upgade `nerdyscout/kicad-exports` to v2.3
2023-10-05 Switch `INTI-CMNB/KiBot` to v2_k6
2023-10-07 Convert symbol lib new format
2023-10-07 Fix footprints
2023-10-07 Squashed 'pcb/kbd/' changes from 41976fe..7d74185
    7d74185 Fix footprints
    git-subtree-dir: pcb/kbd
    git-subtree-split: 7d741855d240a547847f258a2e0e18a2b7158eb2
2023-10-07 Squashed 'pcb/kbd/' changes from 7d74185..53b71bc
    53b71bc Fix ref size
    git-subtree-dir: pcb/kbd
    git-subtree-split: 53b71bc4bfd7a9b551b3a8283b9c1c7a54f56529
2023-10-16 Add new plate data for new version
2023-10-16 Fix position
2023-10-16 Squashed 'pcb/kbd/' changes from 53b71bc..b377b10
    b377b10 Fix position
    git-subtree-dir: pcb/kbd
    git-subtree-split: b377b107aabd5b0266aa88b4489bf3631e9000c8
2023-10-18 Squashed 'pcb/kbd/' changes from b377b10..7fb7779
    7fb7779 Update choc socket
    git-subtree-dir: pcb/kbd
    git-subtree-split: 7fb777965bbec1add41354a3065d91e341473b00
2023-10-18 Update directory trees
2023-10-18 Update filenames
2023-10-18 Add 1.5u
2023-10-18 Remove kbd dir
2023-10-18 Add choc with rotary encoder
2023-10-18 Update pad name
2023-10-18 Squashed 'pcb/common/kbd/' changes from b6de4ec..805f605
    805f605 Update pad name
    git-subtree-dir: pcb/common/kbd
    git-subtree-split: 805f6051982625c002024dd6c8d945815fc43f40
2023-10-21 Squashed 'pcb/common/kbd/' changes from 805f605..192148e
    192148e Update ref positions
    git-subtree-dir: pcb/common/kbd
    git-subtree-split: 192148e2adc01683c1eab33d901bd1d5faa98ef2
2023-10-21 Adjust hole positions
2023-10-21 Squashed 'pcb/common/kbd/' changes from 192148e..b579ab6
    b579ab6 Adjust hole positions
    git-subtree-dir: pcb/common/kbd
    git-subtree-split: b579ab6b98a189e6aa56a4bafcde5954cc464b0a
2023-10-21 Squashed 'pcb/common/kbd/' changes from b579ab6..51de1d9
    51de1d9 Adjust pad size
    git-subtree-dir: pcb/common/kbd
    git-subtree-split: 51de1d90c9d909ca0fc34986691014b41b4bf398
2023-10-21 Add teardrop
2023-10-21 Update silk
2023-10-21 Fix output path
2023-11-06 Add jlcpcb files
2023-11-06 Update jlcpcb files
2023-11-11 Fix outline
2023-11-11 Fix the thumb key for alps pcb plate
2023-11-12 Update footprints for crkbd4
2023-11-12 Fix choc footprints
2023-11-12 Squashed 'pcb/common/kbd/' changes from 51de1d9..52290c7
    52290c7 fix gateron low profile
    e24354d Fix choc footprints
    d3325a6 Update
    e87945a Update footprints for crkbd4
    git-subtree-dir: pcb/common/kbd
    git-subtree-split: 52290c77f0f5b70e980768bd36c01103892abc8f
2023-11-12 Remove old files
2023-11-25 Update directories
2023-12-01 Update encoder pin
2023-12-03 Add holes for mini
2023-12-03 Add plates for v4
2023-12-03 Rename files
2023-12-15 Update order files
2023-12-15 Update view
2023-12-20 Fix fixed pin
2023-12-20 Remove kbd
2023-12-20 Squashed 'pcbs/common/kbd/' content from commit 43da0ca
    git-subtree-dir: pcbs/common/kbd
    git-subtree-split: 43da0ca3d5e3e0a628e7d64e4fce58097fee60bb
2024-01-26 Update pcb plate files
2024-01-26 Update choc silk
2024-02-13 Update firmware docs
2024-02-23 Add case data
2024-02-27 change stroke color to make them more conspicuous.
2024-03-18 Remove old dir
2024-03-18 Add the mini case
2024-03-30 Fix for #223
2024-03-31 Update firmwaere docs for building yourself
2024-04-19 Fix GND/VCC for mini version
2024-04-24 Squashed 'pcbs/common/kbd/' changes from 930e7d9..a74626e
    a74626e Add PJ-398A-5A_PJ-399B-6A
    143c1ef Merge pull request #12 from jradtilbrook/dir
    f1ece33 Update actions to try get it working
    97ab0a1 Remove hardcoded directory
    git-subtree-dir: pcbs/common/kbd
    git-subtree-split: a74626e46144006eab4c529c62625212847dd795
2024-04-24 Squashed 'pcbs/common/kbd/' changes from a74626e..c53bf51
    c53bf51 Fix pin name
    git-subtree-dir: pcbs/common/kbd
    git-subtree-split: c53bf519ed9e0a498869ab56d44385f89ec54b36
2024-05-30 ファームウェアのリンク切れを修正
    おそらくV4が出たことにより、ファームウェアのリンクが切れていたので、urlの修正を提案させていただきます。
2024-06-09 Point dead links towards approriate version of firmware guide.
2024-10-18 Change 4 layer left side
2024-11-15 Add a caution for EMI issue
2024-12-04 Move MCU to the center of the PCB
2024-12-04 Generate production files
2024-12-20 Fix link to docs/firmware
2025-01-03 Add Corne Chocolate v4.1.1
2025-01-16 Update production files
2025-04-14 Fix typo in buildguide_en.md
